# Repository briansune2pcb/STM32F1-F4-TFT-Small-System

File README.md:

# STM32F1-F4-TFT-Small-System

These example PCB are designed under Eagle 6.1 CAD.

The PCB including TFT and audio codec vs1003.

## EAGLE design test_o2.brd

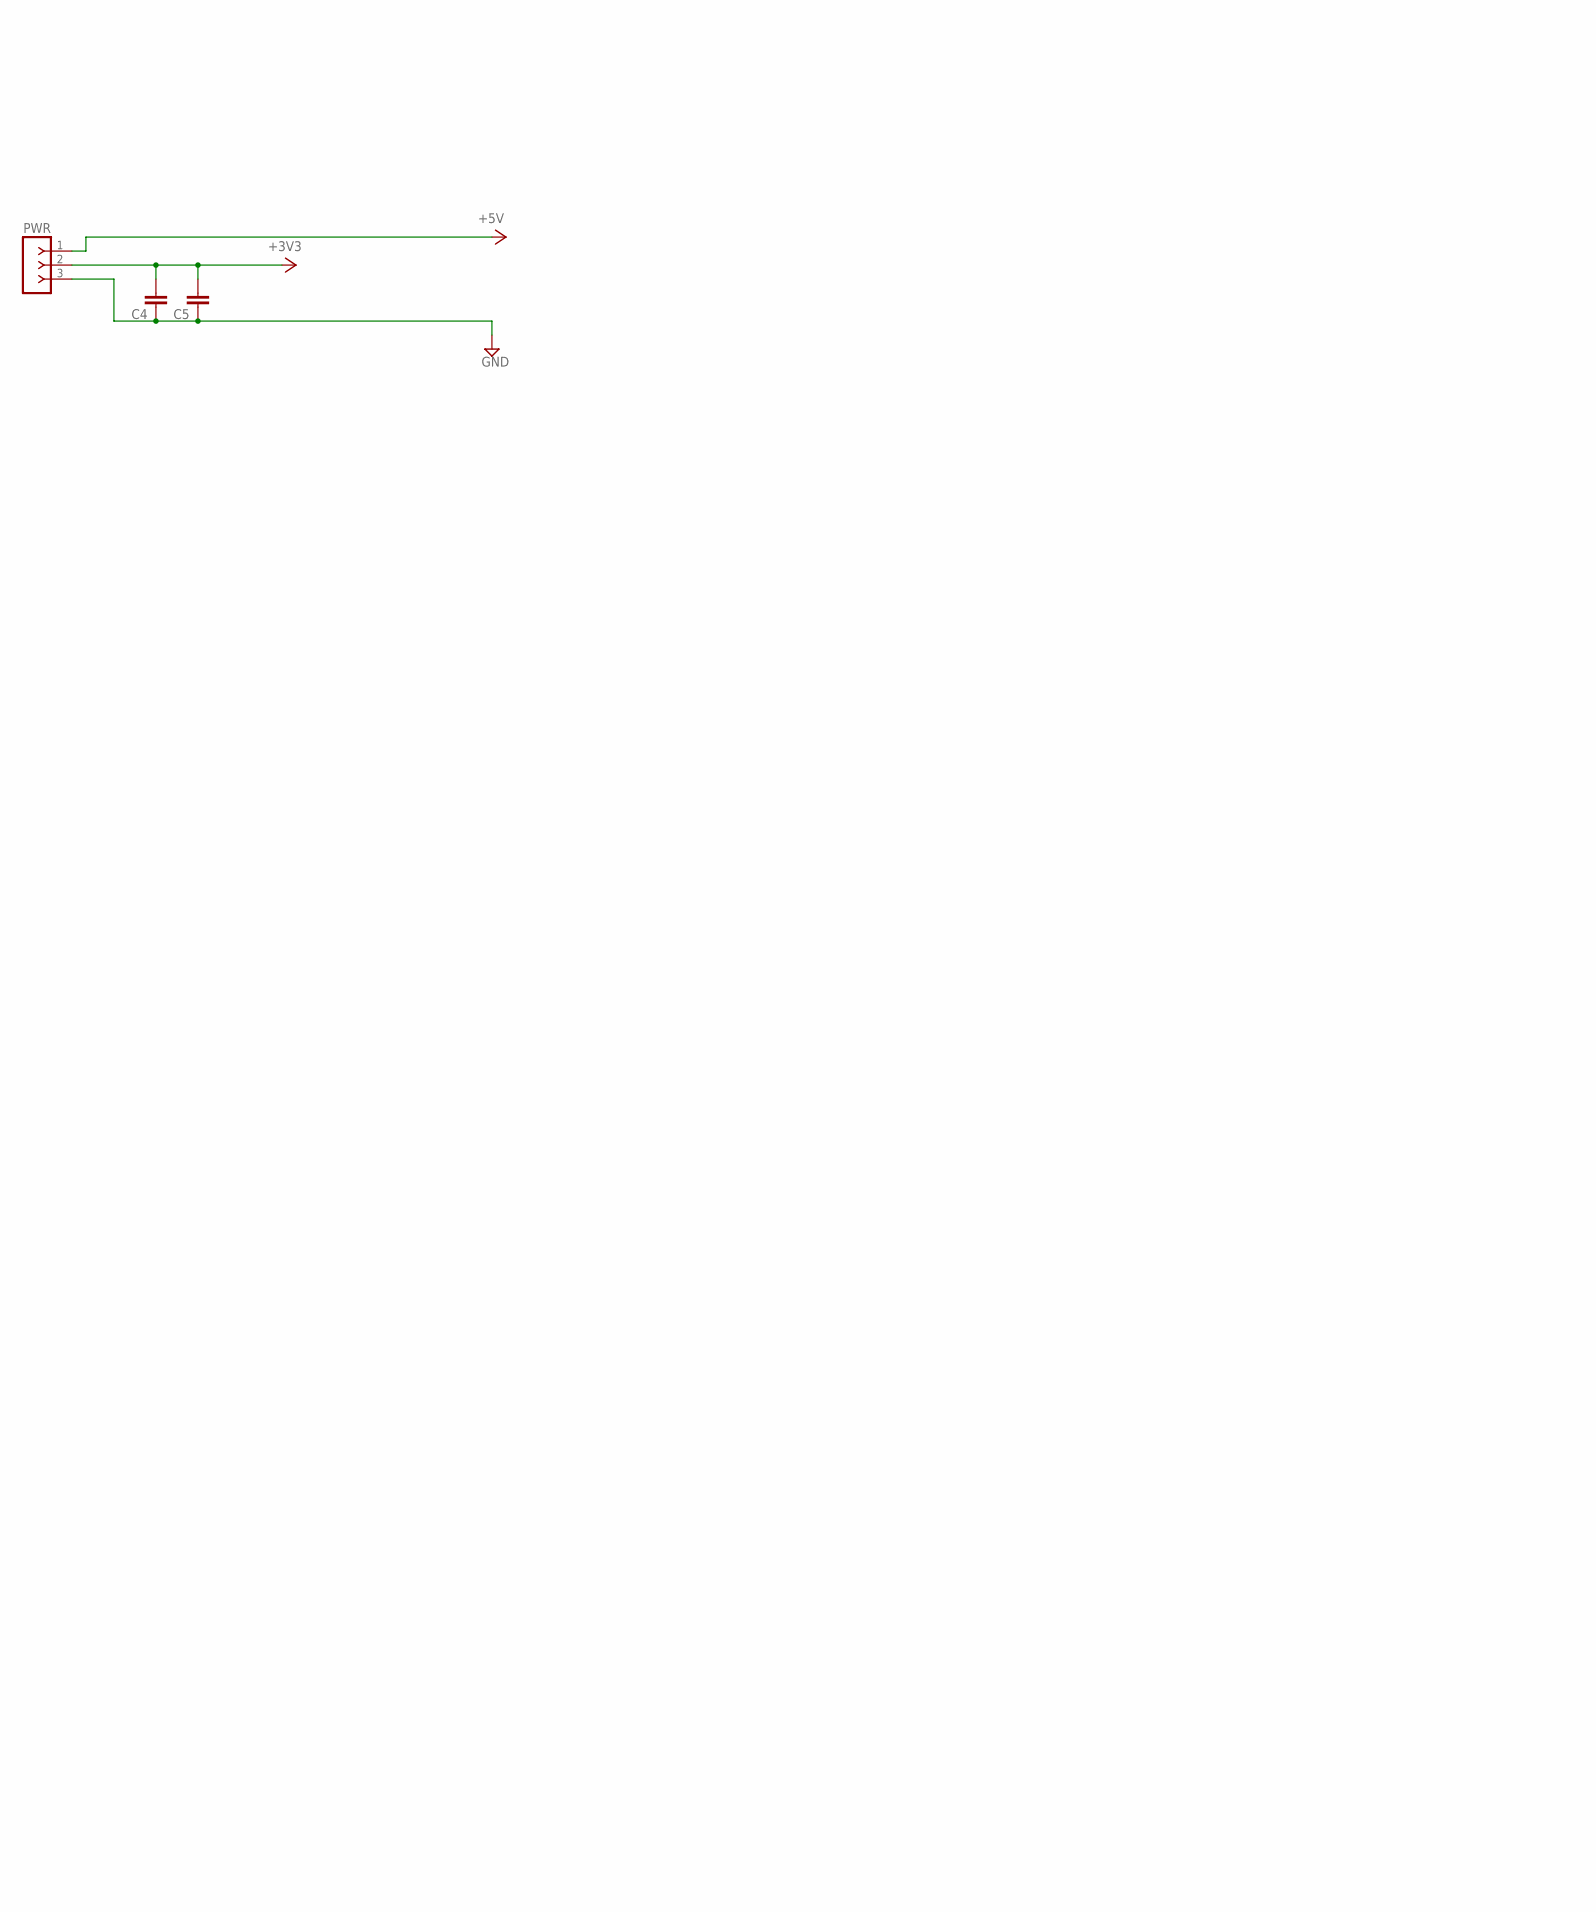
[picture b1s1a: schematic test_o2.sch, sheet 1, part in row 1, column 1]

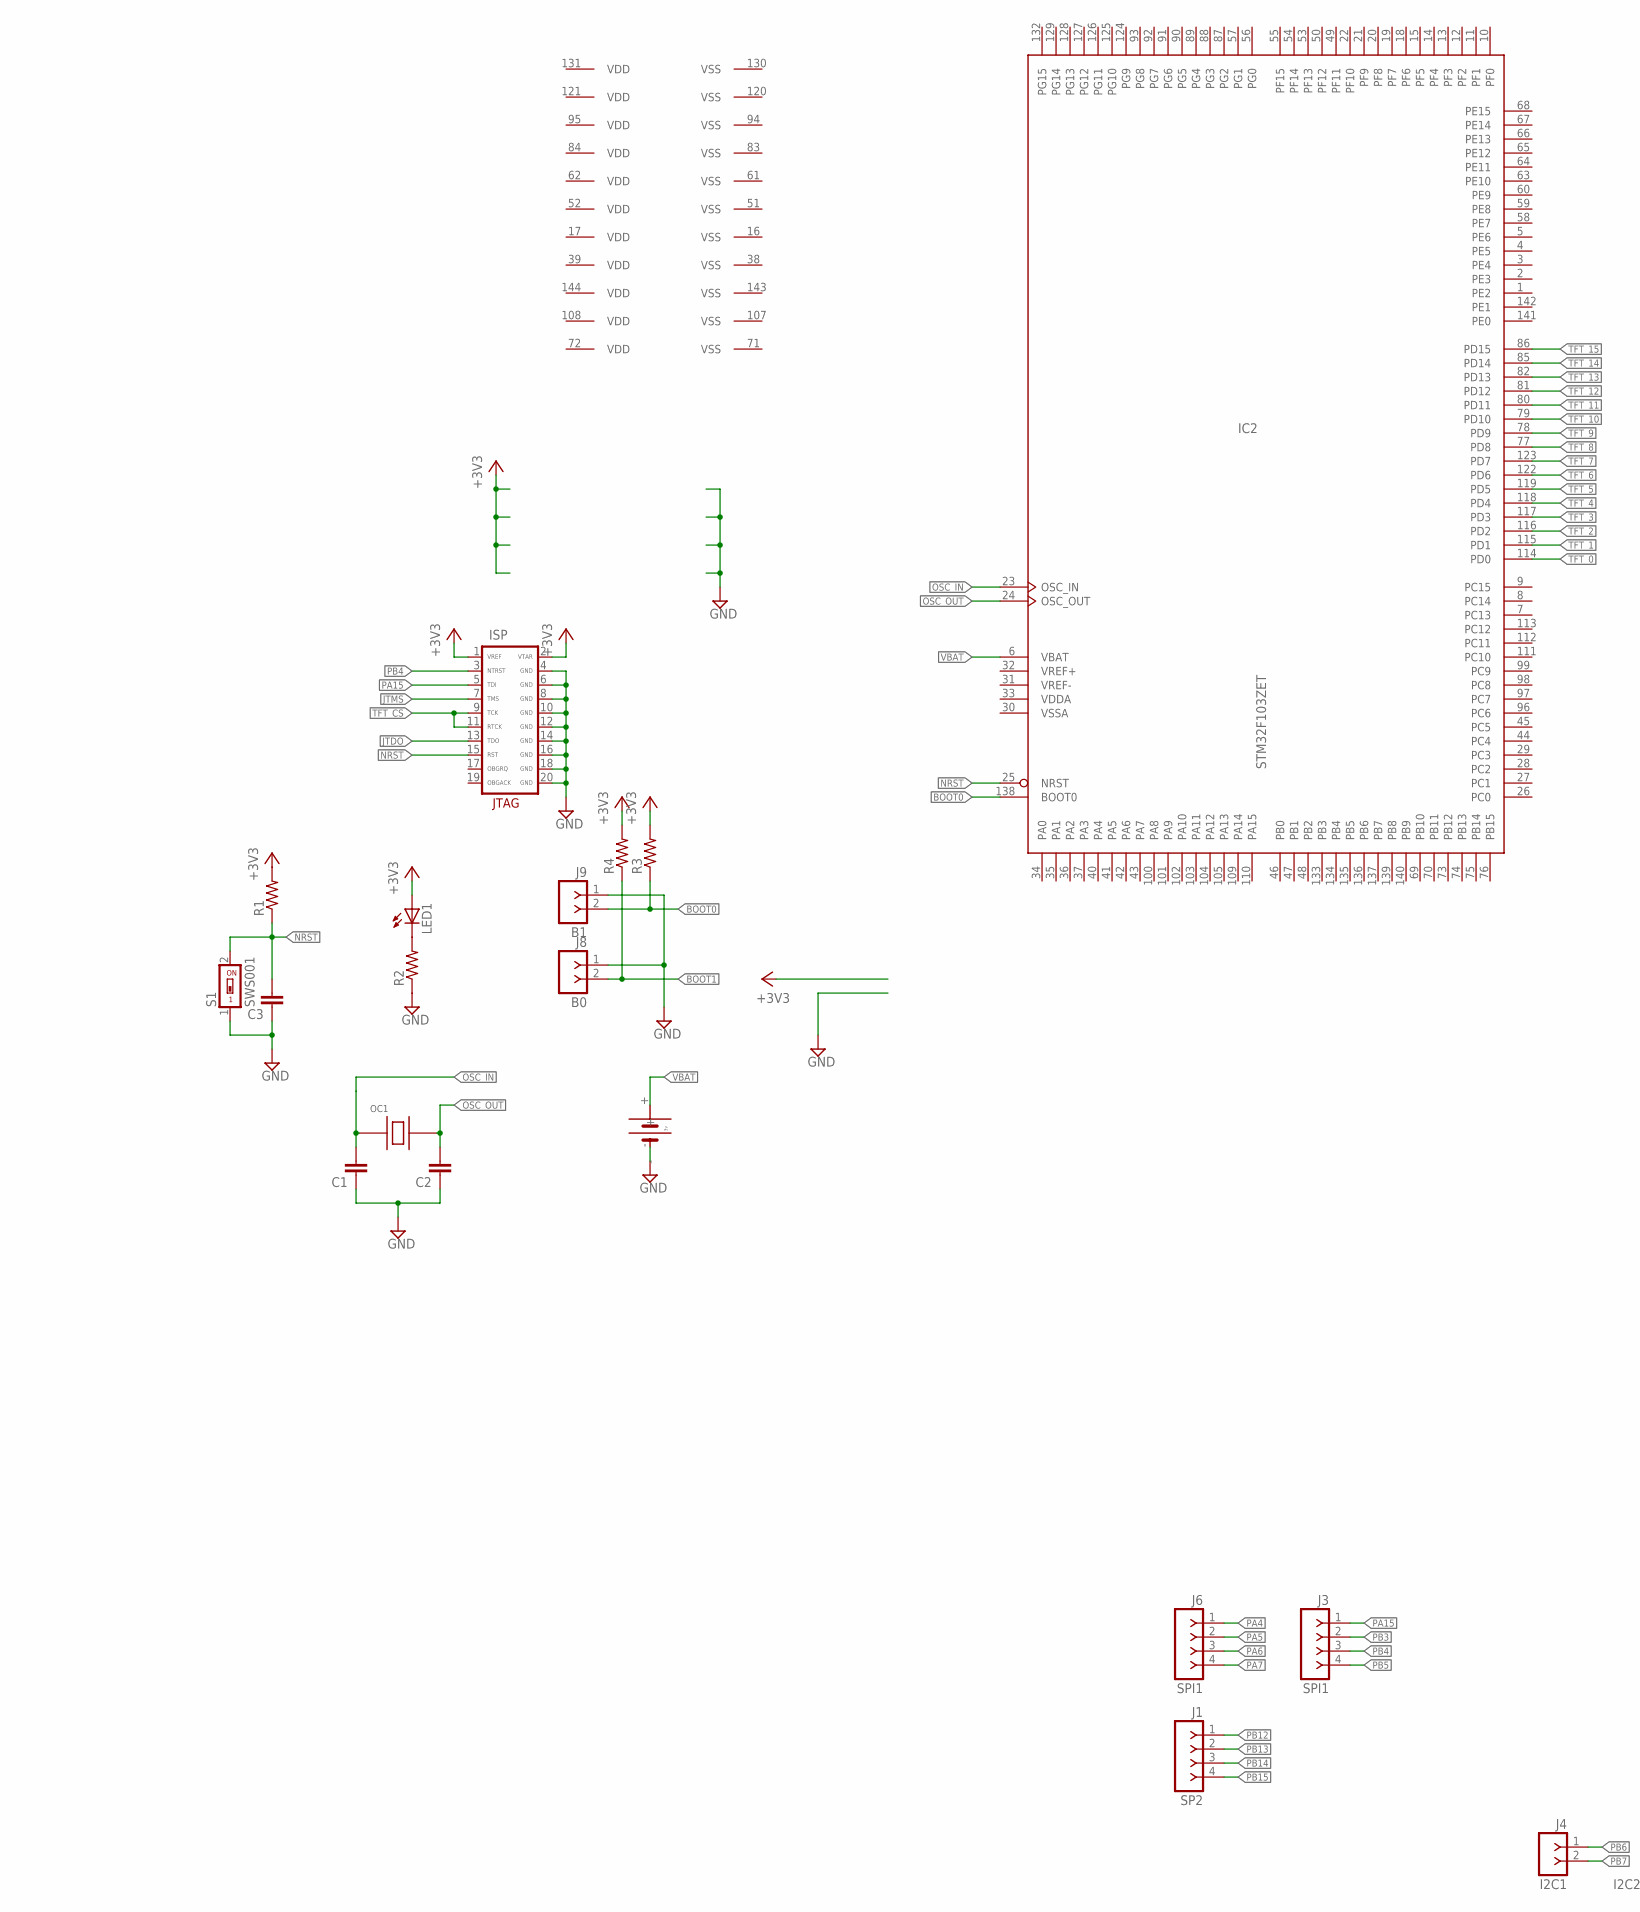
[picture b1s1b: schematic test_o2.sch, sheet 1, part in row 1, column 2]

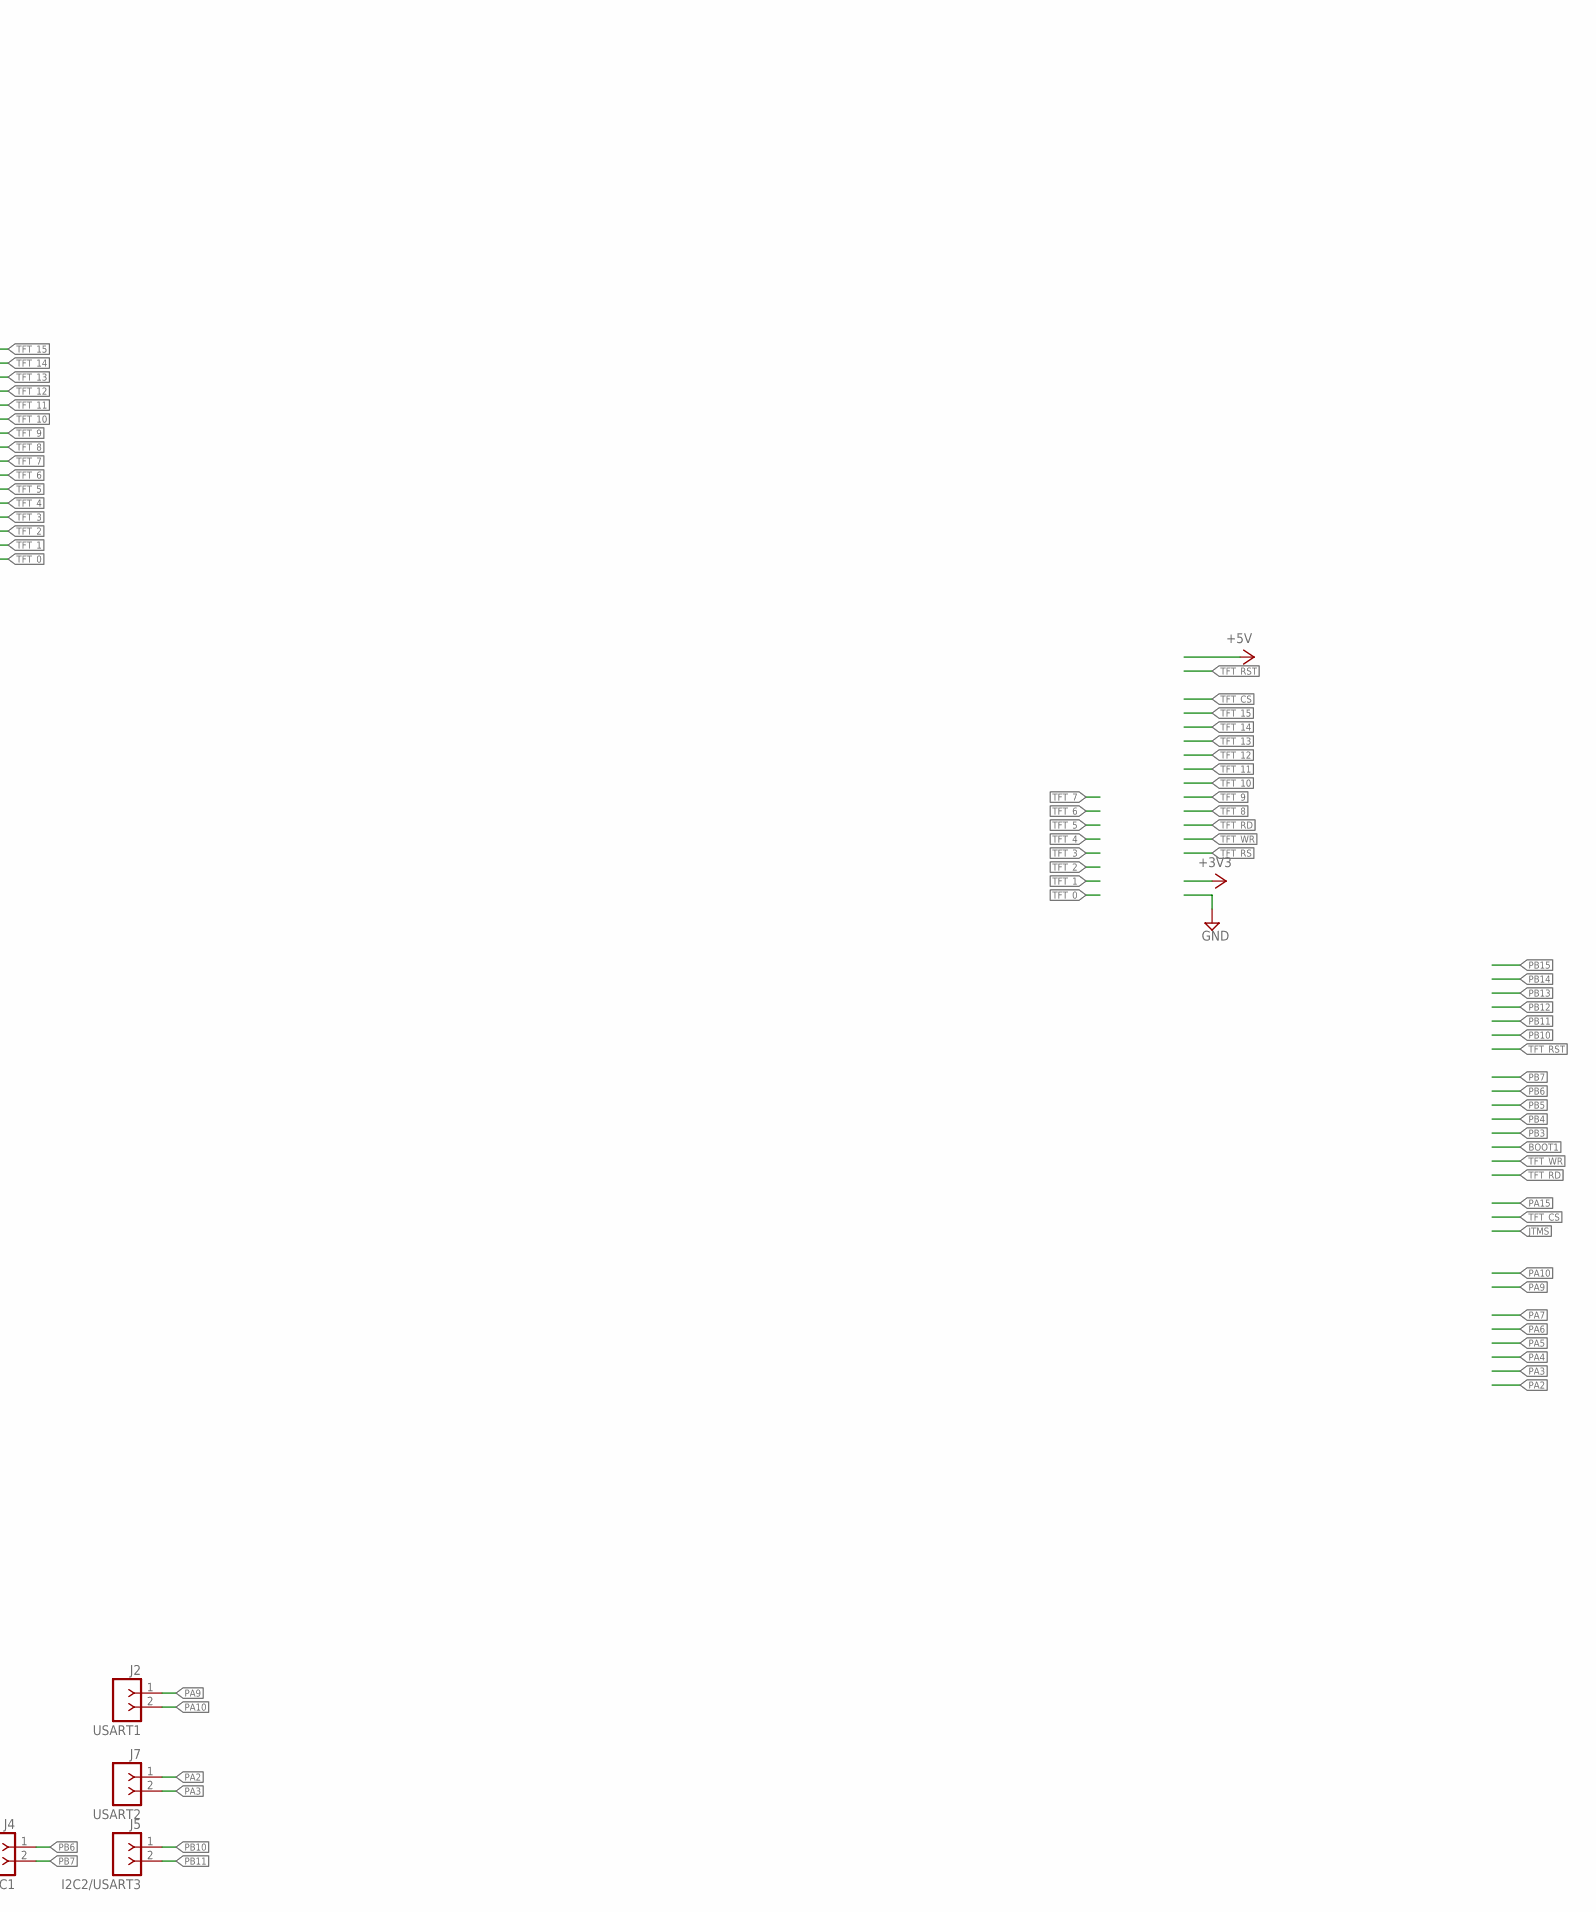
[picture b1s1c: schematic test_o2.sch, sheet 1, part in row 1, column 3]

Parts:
C1, C2, C3, C4, C5: C-EUC1206; C1206
IC2: STM32F103ZET; LQFP144
ISP: JTAG; PAK100/2500-20
J1: SP2; SIP-100-04-40
J2: USART1; SIP-100-02-40
J3, J6: SPI1; SIP-100-04-40
J4: I2C1; SIP-100-02-40
J5: I2C2/USART3; SIP-100-02-40
J7: USART2; SIP-100-02-40
J8: B0; SIP-100-02-40
J9: B1; SIP-100-02-40
LED1: LEDSML1206; SML1206
OC1: SMAQ-7050B; IQG7050B
PWR: F-1X03-SIP-100-40; SIP-100-03-40
R1, R2, R3, R4: R-US_R1206; R1206
S1: SWS001; SMS-001
U$2: 1220BATTERY_SF; 1220BATTERY

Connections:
+3V3: C4.2, C5.2, ISP.1 (VREF), ISP.2 (VTAR), LED1.A, PWR.2, R1.2, R3.2, R4.2; also elsewhere on the board
+5V: PWR.1; also elsewhere on the board
BOOT0: IC2.138 (BOOT0), J9.2, R3.1
BOOT1: J8.2, R4.1
GND: C1.1, C2.1, C3.1, C4.1, C5.1, ISP.4 (GND), ISP.6 (GND), ISP.8 (GND), ISP.10 (GND), ISP.12 (GND), ISP.14 (GND), ISP.16 (GND), ISP.18 (GND), ISP.20 (GND), J8.1, J9.1, PWR.3, R2.1, S1.1, U$2.-; also elsewhere on the board
JTDO: ISP.13 (TDO)
JTMS: ISP.7 (TMS)
unnamed: LED1.C, R2.2
NRST: C3.2, IC2.25 (NRST), ISP.15 (RST), R1.1, S1.2
OSC_IN: C1.2, IC2.23 (OSC_IN), OC1.P$1 (PIN1)
OSC_OUT: C2.2, IC2.24 (OSC_OUT), OC1.P$3 (PIN2)
PA2: J7.1
PA3: J7.2
PA4: J6.1
PA5: J6.2
PA6: J6.3
PA7: J6.4
PA9: J2.1
PA10: J2.2
PA15: ISP.5 (TDI), J3.1
PB3: J3.2
PB4: ISP.3 (NTRST), J3.3
PB5: J3.4
PB6: J4.1
PB7: J4.2
PB10: J5.1
PB11: J5.2
PB12: J1.1
PB13: J1.2
PB14: J1.3
PB15: J1.4
TFT_0: IC2.114 (PD0); also elsewhere on the board
TFT_1: IC2.115 (PD1); also elsewhere on the board
TFT_2: IC2.116 (PD2); also elsewhere on the board
TFT_3: IC2.117 (PD3); also elsewhere on the board
TFT_4: IC2.118 (PD4); also elsewhere on the board
TFT_5: IC2.119 (PD5); also elsewhere on the board
TFT_6: IC2.122 (PD6); also elsewhere on the board
TFT_7: IC2.123 (PD7); also elsewhere on the board
TFT_8: IC2.77 (PD8); also elsewhere on the board
TFT_9: IC2.78 (PD9); also elsewhere on the board
TFT_10: IC2.79 (PD10); also elsewhere on the board
TFT_11: IC2.80 (PD11); also elsewhere on the board
TFT_12: IC2.81 (PD12); also elsewhere on the board
TFT_13: IC2.82 (PD13); also elsewhere on the board
TFT_14: IC2.85 (PD14); also elsewhere on the board
TFT_15: IC2.86 (PD15); also elsewhere on the board
TFT_CS: ISP.9 (TCK), ISP.11 (RTCK); also elsewhere on the board
VBAT: IC2.6 (VBAT), U$2.+
VDD: IC2.17 (VDD), IC2.39 (VDD), IC2.52 (VDD), IC2.62 (VDD), IC2.72 (VDD), IC2.84 (VDD), IC2.95 (VDD), IC2.108 (VDD), IC2.121 (VDD), IC2.131 (VDD), IC2.144 (VDD)
VDDA: IC2.33 (VDDA)
VREF+: IC2.32 (VREF+)
VREF-: IC2.31 (VREF-)
VSS: IC2.16 (VSS), IC2.38 (VSS), IC2.51 (VSS), IC2.61 (VSS), IC2.71 (VSS), IC2.83 (VSS), IC2.94 (VSS), IC2.107 (VSS), IC2.120 (VSS), IC2.130 (VSS), IC2.143 (VSS)
VSSA: IC2.30 (VSSA)

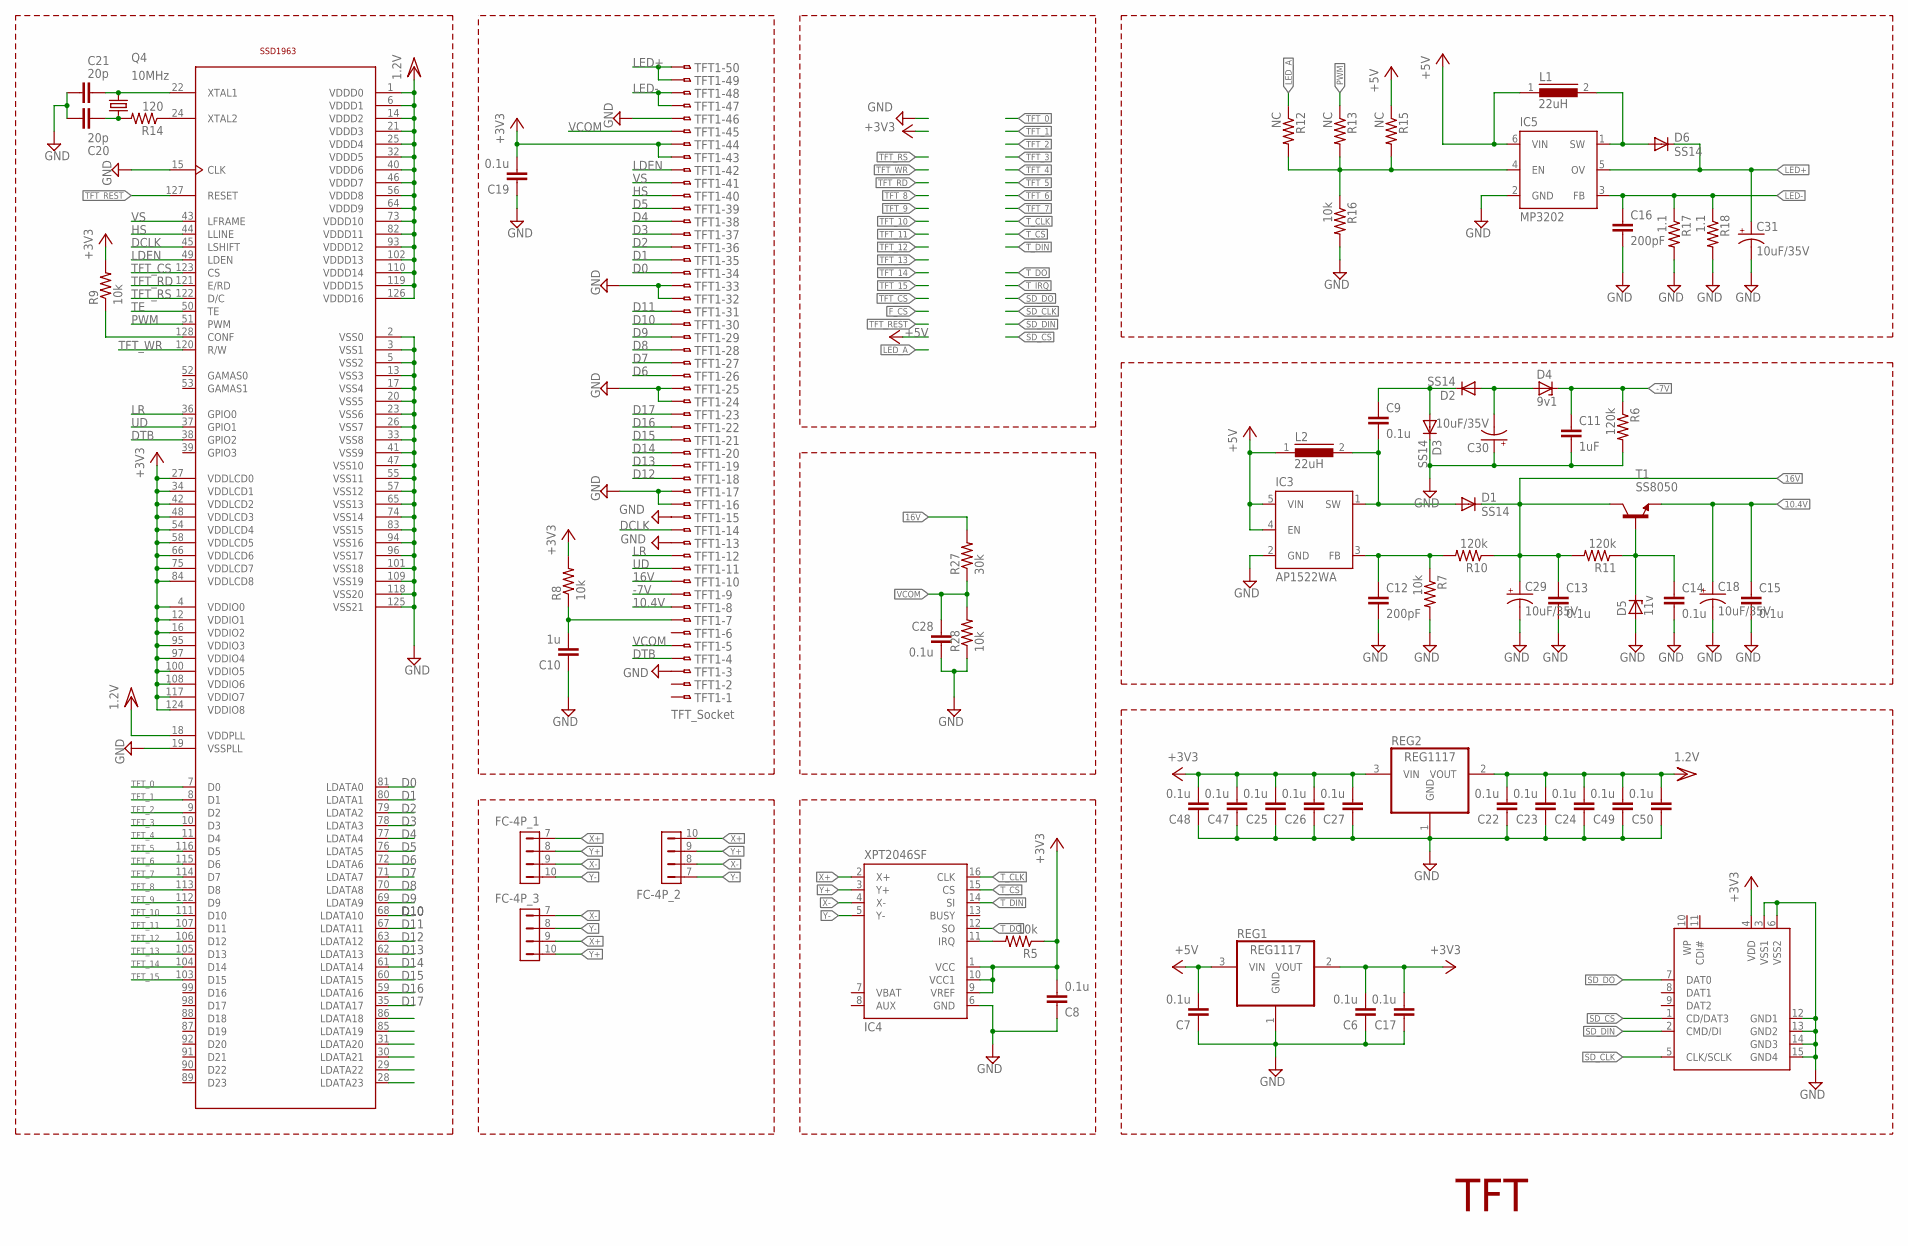
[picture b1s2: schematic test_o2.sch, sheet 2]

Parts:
C6, C7, C8, C9, C13, C14, C15, C17, C19, C22, C23, C24, C25, C26, C27, C28, C47, C48, C49, C50: 0.1u; C0805
C10: 1u; C0805
C11: 1uF; C0805
C12, C16: 200pF; C0805
C18, C29, C30, C31: 10uF/35V; B/3528-21R
C20, C21: 20p; C0805
D1, D2, D3, D6: SS14; DO214AC
D4: 9v1; SOD80C
D5: 11v; SOD80C
FC-4P_1, FC-4P_2, FC-4P_3: FH12-04S-1S; FH12-4S-1SH
IC1: SSD1963LQFP; LQFP128
IC3: AP1522WA; SOT23-5L
IC4: XPT2046SF; TSSOP16L
IC5: MP3202; SOT23-6L
L1, L2: 22uH; DR74
Q4: 10MHz; HC49UP
R5, R7, R16: 10k; R0805
R6, R10, R11: 120k; R0805
R8, R9, R28: 10k; M0805
R12, R13, R15: NC; R0805
R14: 120; M0805
R17, R18: 1.1; R0805
R27: 30k; M0805
REG1, REG2: REG1117; SOT223; MPN REG1117
SOC_1: MMC/SD; SDCMF-10915W010
T1: SS8050; SOT23
TFT1: TFT_Socket; 50

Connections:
10.4V: C15.1, C18.+, T1.2 (E), TFT1.8
16V: C13.1, C29.+, D1.C, R10.1, R11.2, R27.2, T1.3 (C), TFT1.10
+3V3: C6.2, C8.2, C17.2, C19.2, C25.2, C26.2, C27.2, C47.2, C48.2, IC1.4 (VDDIO0), IC1.12 (VDDIO1), IC1.16 (VDDIO2), IC1.27 (VDDLCD0), IC1.34 (VDDLCD1), IC1.42 (VDDLCD2), IC1.48 (VDDLCD3), IC1.54 (VDDLCD4), IC1.58 (VDDLCD5), IC1.66 (VDDLCD6), IC1.75 (VDDLCD7), IC1.84 (VDDLCD8), IC1.95 (VDDIO3), IC1.97 (VDDIO4), IC1.100 (VDDIO5), IC1.108 (VDDIO6), IC1.117 (VDDIO7), IC1.124 (VDDIO8), IC4.1 (VCC), IC4.9 (VREF), IC4.10 (VCC1), R5.1, R8.2, R9.2, REG1.2 (VOUT), REG2.3 (VIN), SOC_1.4 (VDD), TFT1.43, TFT1.44; also elsewhere on the board
+5V: C7.2, IC3.4 (EN), IC3.5 (VIN), IC5.6 (VIN), L1.1, L2.1, R15.1, REG1.3 (VIN); also elsewhere on the board
-7V: C11.1, D4.C, R6.1, TFT1.9
D0: IC1.81 (LDATA0), TFT1.34
D1: IC1.80 (LDATA1), TFT1.35
D2: IC1.79 (LDATA2), TFT1.36
D3: IC1.78 (LDATA3), TFT1.37
D4: IC1.77 (LDATA4), TFT1.38
D5: IC1.76 (LDATA5), TFT1.39
D6: IC1.72 (LDATA6), TFT1.26
D7: IC1.71 (LDATA7), TFT1.27
D8: IC1.70 (LDATA8), TFT1.28
D9: IC1.69 (LDATA9), TFT1.29
D10: IC1.68 (LDATA10), TFT1.30
D11: IC1.67 (LDATA11), TFT1.31
D12: IC1.63 (LDATA12), TFT1.18
D13: IC1.62 (LDATA13), TFT1.19
D14: IC1.61 (LDATA14), TFT1.20
D15: IC1.60 (LDATA15), TFT1.21
D16: IC1.59 (LDATA16), TFT1.22
D17: IC1.35 (LDATA17), TFT1.23
DCLK: IC1.45 (LSHIFT), TFT1.14
DTB: IC1.38 (GPIO2), TFT1.4
GND: C6.1, C7.1, C8.1, C10.1, C11.2, C12.2, C13.2, C14.2, C15.2, C16.2, C17.1, C18.-, C19.1, C20.1, C21.1, C22.1, C23.1, C24.1, C25.1, C26.1, C27.1, C28.2, C29.-, C30.+, C31.-, C47.1, C48.1, C49.1, C50.1, D3.C, D5.A, IC1.2 (VSS0), IC1.3 (VSS1), IC1.5 (VSS2), IC1.13 (VSS3), IC1.15 (CLK), IC1.17 (VSS4), IC1.19 (VSSPLL), IC1.20 (VSS5), IC1.23 (VSS6), IC1.26 (VSS7), IC1.33 (VSS8), IC1.41 (VSS9), IC1.47 (VSS10), IC1.55 (VSS11), IC1.57 (VSS12), IC1.65 (VSS13), IC1.74 (VSS14), IC1.83 (VSS15), IC1.94 (VSS16), IC1.96 (VSS17), IC1.101 (VSS18), IC1.109 (VSS19), IC1.118 (VSS20), IC1.125 (VSS21), IC3.2 (GND), IC4.6 (GND), IC5.2 (GND), R6.2, R7.2, R16.2, R17.2, R18.2, R28.1, REG1.1 (GND), REG2.1 (GND), SOC_1.3 (VSS1), SOC_1.6 (VSS2), SOC_1.12 (GND1), SOC_1.13 (GND2), SOC_1.14 (GND3), SOC_1.15 (GND4), TFT1.3, TFT1.13, TFT1.15, TFT1.16, TFT1.17, TFT1.24, TFT1.25, TFT1.32, TFT1.33, TFT1.46; also elsewhere on the board
HS: IC1.44 (LLINE), TFT1.40
LDEN: IC1.49 (LDEN), TFT1.42
LED+: C31.+, D6.C, IC5.5 (OV), TFT1.49, TFT1.50
LED-: C16.1, IC5.3 (FB), R17.1, R18.1, TFT1.47, TFT1.48
LED_A: R12.1
LR: IC1.36 (GPIO0), TFT1.12
unnamed: IC1.24 (XTAL2), R14.1
unnamed: C9.2, D1.A, IC3.1 (SW), L2.2
unnamed: C9.1, D2.C, D3.A
unnamed: C30.-, D2.A, D4.A
unnamed: C12.1, IC3.3 (FB), R7.1, R10.2
unnamed: D6.A, IC5.1 (SW), L1.2
unnamed: C14.1, D5.C, R11.1, T1.1 (B)
unnamed: IC5.4 (EN), R12.2, R13.2, R15.2, R16.1
unnamed: C21.2, IC1.22 (XTAL1), Q4.2
unnamed: C20.2, Q4.1, R14.2
unnamed: IC1.128 (CONF), R9.1
unnamed: C10.2, R8.1, TFT1.7
PWM: IC1.51 (PWM), R13.1
SD_CLK: SOC_1.5 (CLK/SCLK)
SD_CS: SOC_1.1 (CD/DAT3)
SD_DIN: SOC_1.2 (CMD/DI)
SD_DO: SOC_1.7 (DAT0)
TE: IC1.50 (TE)
TFT_0: IC1.7 (D0); also elsewhere on the board
TFT_1: IC1.8 (D1); also elsewhere on the board
TFT_2: IC1.9 (D2); also elsewhere on the board
TFT_3: IC1.10 (D3); also elsewhere on the board
TFT_4: IC1.11 (D4); also elsewhere on the board
TFT_5: IC1.116 (D5); also elsewhere on the board
TFT_6: IC1.115 (D6); also elsewhere on the board
TFT_7: IC1.114 (D7); also elsewhere on the board
TFT_8: IC1.113 (D8); also elsewhere on the board
TFT_9: IC1.112 (D9); also elsewhere on the board
TFT_10: IC1.111 (D10); also elsewhere on the board
TFT_11: IC1.107 (D11); also elsewhere on the board
TFT_12: IC1.106 (D12); also elsewhere on the board
TFT_13: IC1.105 (D13); also elsewhere on the board
TFT_14: IC1.104 (D14); also elsewhere on the board
TFT_15: IC1.103 (D15); also elsewhere on the board
TFT_CS: IC1.123 (CS); also elsewhere on the board
TFT_RD: IC1.121 (E/RD)
TFT_REST: IC1.127 (RESET)
TFT_RS: IC1.122 (D/C)
TFT_WR: IC1.120 (R/W)
T_CLK: IC4.16 (CLK)
T_CS: IC4.15 (CS)
T_DIN: IC4.14 (SI)
T_DO: IC4.12 (SO)
T_IRQ: IC4.11 (IRQ), R5.2
UD: IC1.37 (GPIO1), TFT1.11
VCC/2: C22.2, C23.2, C24.2, C49.2, C50.2, IC1.1 (VDDD0), IC1.6 (VDDD1), IC1.14 (VDDD2), IC1.18 (VDDPLL), IC1.21 (VDDD3), IC1.25 (VDDD4), IC1.32 (VDDD5), IC1.40 (VDDD6), IC1.46 (VDDD7), IC1.56 (VDDD8), IC1.64 (VDDD9), IC1.73 (VDDD10), IC1.82 (VDDD11), IC1.93 (VDDD12), IC1.102 (VDDD13), IC1.110 (VDDD14), IC1.119 (VDDD15), IC1.126 (VDDD16), REG2.2 (VOUT)
VCOM: C28.1, R27.1, R28.2, TFT1.5, TFT1.45
VS: IC1.43 (LFRAME), TFT1.41
X+: FC-4P_1.7 (1), FC-4P_2.10 (4), FC-4P_3.9 (3), IC4.2 (X+)
X-: FC-4P_1.9 (3), FC-4P_2.8 (2), FC-4P_3.7 (1), IC4.4 (X-)
Y+: FC-4P_1.8 (2), FC-4P_2.9 (3), FC-4P_3.10 (4), IC4.3 (Y+)
Y-: FC-4P_1.10 (4), FC-4P_2.7 (1), FC-4P_3.8 (2), IC4.5 (Y-)

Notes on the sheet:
TFT

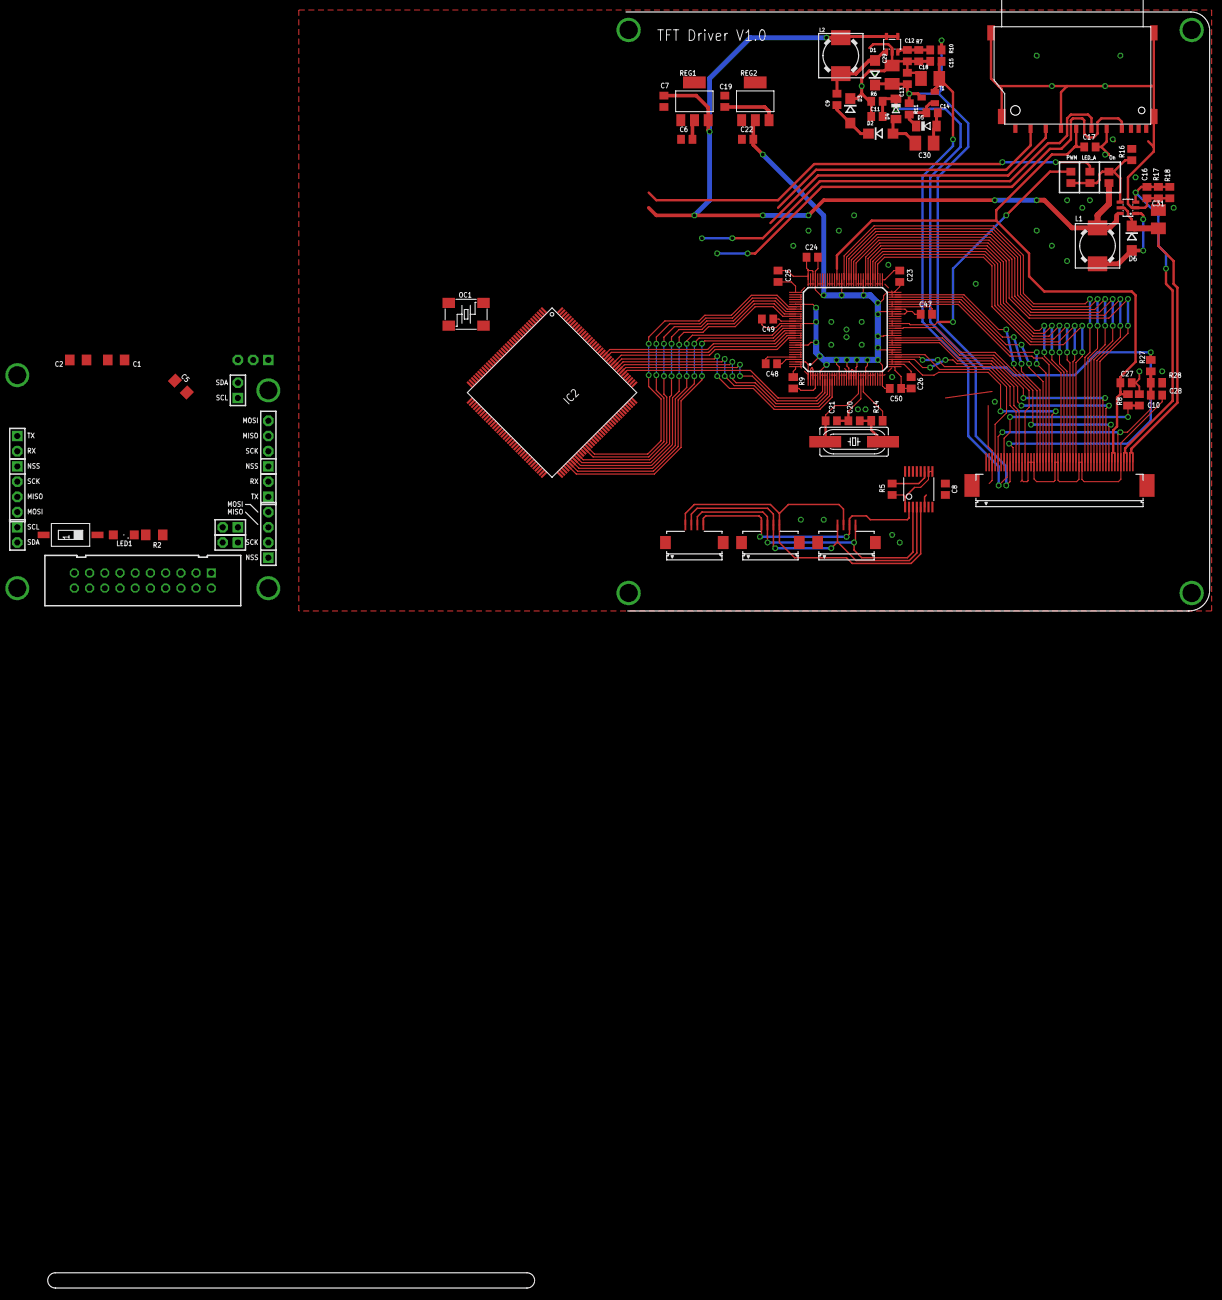
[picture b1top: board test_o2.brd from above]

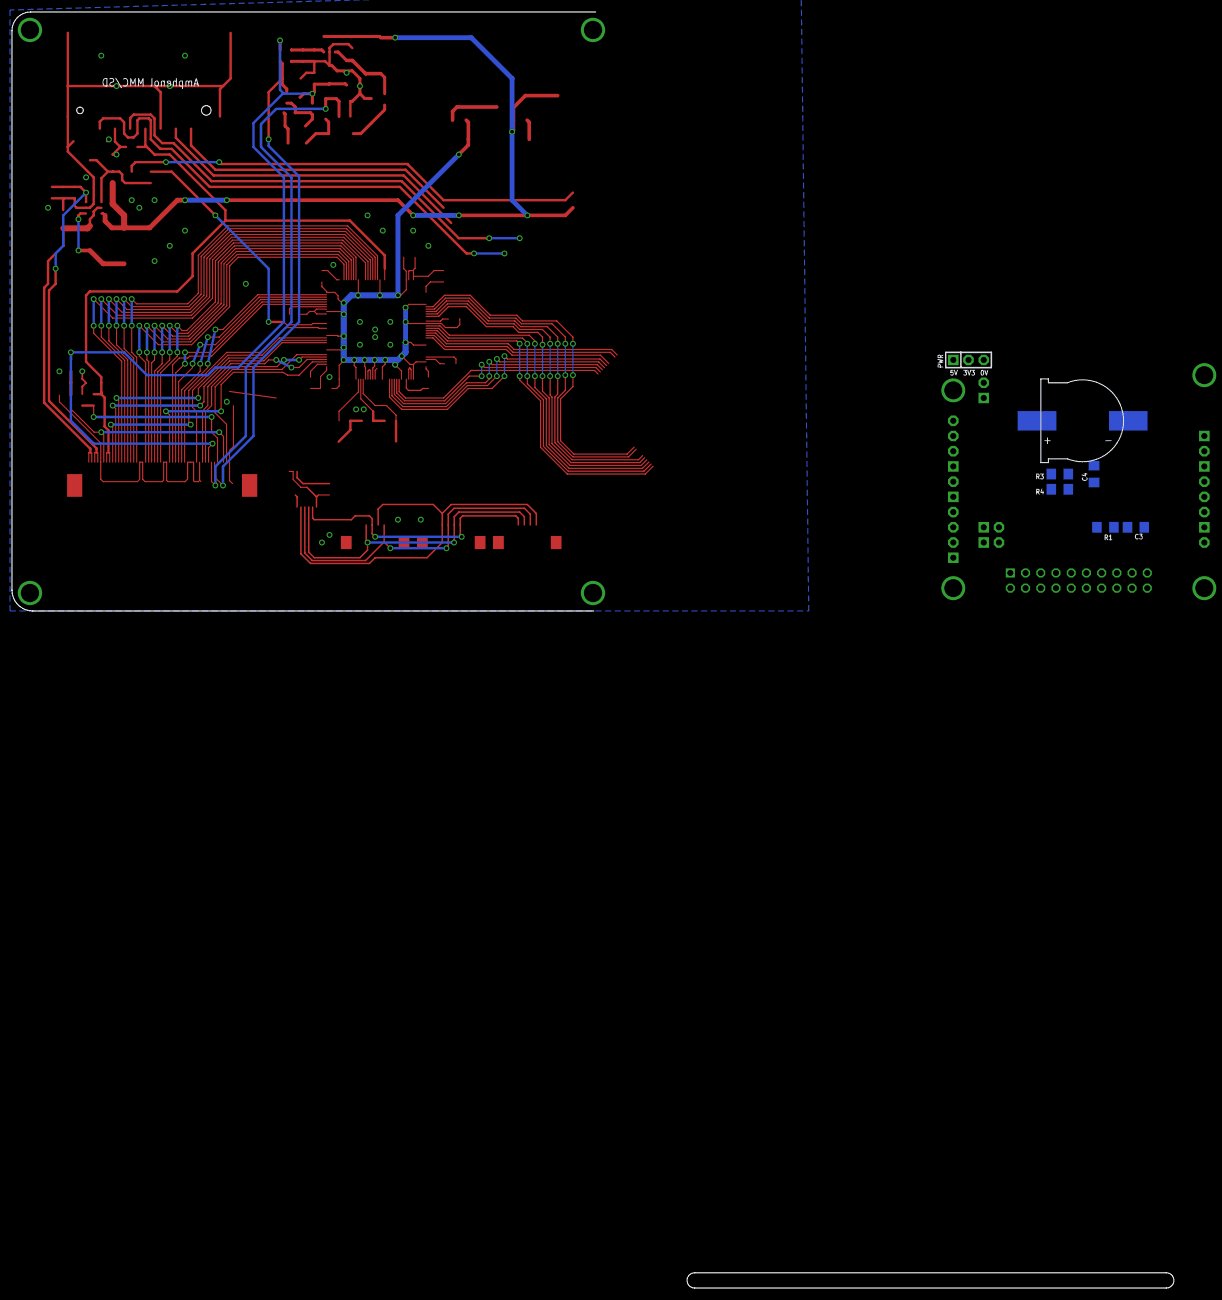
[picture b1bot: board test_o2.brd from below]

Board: 2 copper layers, 194.0 x 213.0 mm, 92 parts (7 on the bottom side), 81 nets.

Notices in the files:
parts and their libraries:
con-headers-jp: Copyright (C) 2008, Bob Starr
atmel-arm: Copyright (C) 2008-2009, Bob Starr
